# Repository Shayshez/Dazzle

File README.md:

# Dazzle
## CC-BY-SA 4.0
Rotatable Dual VC-Polarizer and VCA, Based on MI "Blinds".

## ROTATABLE = Modules for 3u / 1u
Dazzle comes with 2 panels: 1u/20hp and 3u/6hp

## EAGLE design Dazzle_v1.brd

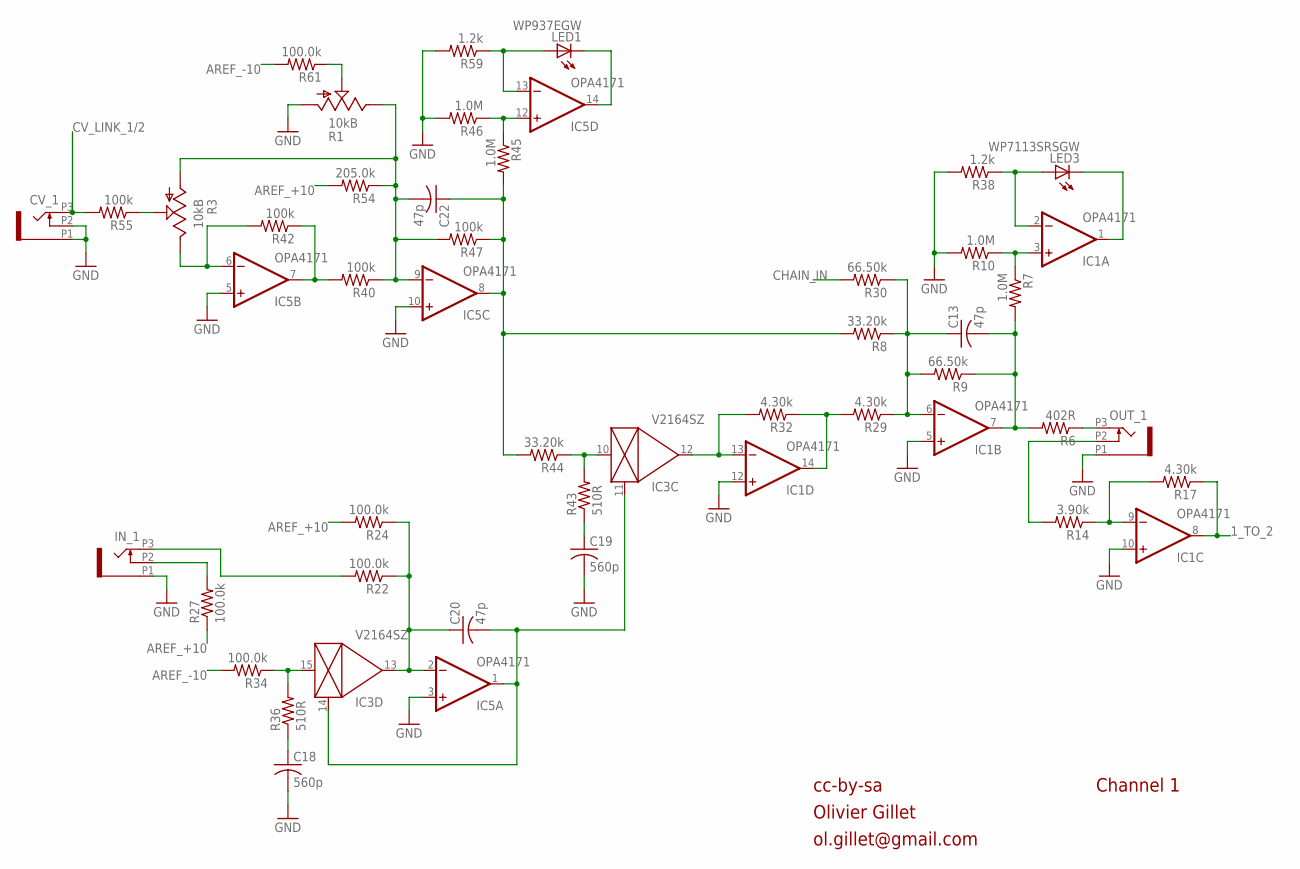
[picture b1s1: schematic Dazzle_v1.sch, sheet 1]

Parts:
C13, C20, C22: 47p; C0603
C18, C19: 560p; C0603
CV_1: OG-PJ301_PJ301_THONKICONN; OG-PJ301_WQP_PJ_301M6_NO_HOLE
IC1, IC5: OPA4171; TSSOP14
IC3: V2164SZ; SOIC16N
IN_1: OG-PJ301_PJ301_THONKICONN; OG-PJ301_WQP_PJ_301M6_NO_HOLE
LED1: WP937EGW; LED3MM
LED3: WP7113SRSGW; LED5MM
OUT_1: OG-PJ301_PJ301_THONKICONN; OG-PJ301_WQP_PJ_301M6_NO_HOLE
R1: 10kB; ALPS_POT_VERTICAL_PS
R3: 10kB; POT-ALPS_ALPS_POT_VERTICAL_PS
R6: 402R; R0603
R7, R10, R45, R46: 1.0M; R0603
R8, R44: 33.20k; R0603
R9, R30: 66.50k; R0603
R14: 3.90k; R0603
R17, R29, R32: 4.30k; R0603
R22, R24, R27, R34, R61: 100.0k; R0603
R36, R43: 510R; R0603
R38, R59: 1.2k; R0603
R40, R42, R47, R55: 100k; R0603
R54: 205.0k; R0603

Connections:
1_TO_2: IC1.8 (OUT), R17.1; also elsewhere on the board
AREF_+10: R24.2, R27.1, R54.2; also elsewhere on the board
AREF_-10: R34.2, R61.2; also elsewhere on the board
CHAIN_IN: R30.2; also elsewhere on the board
CV_LINK_1/2: CV_1.P3 (3), R55.2; also elsewhere on the board
FOO: IC3.15 (IN), R34.1, R36.2
GAIN_1: C22.1, IC5.8 (OUT), R8.2, R44.2, R45.2, R47.1
GND: C18.2, C19.2, CV_1.P1 (1), CV_1.P2 (2), IC1.5 (+IN), IC1.10 (+IN), IC1.12 (+IN), IC5.3 (+IN), IC5.5 (+IN), IC5.10 (+IN), IN_1.P1 (1), OUT_1.P1 (1), R1.P$3 (A), R10.2, R38.2, R46.2, R59.2; also elsewhere on the board
unnamed: R1.P$2 (S), R61.1
unnamed: IC1.13 (-IN), IC3.12 (OUT), R32.2
unnamed: IC5.14 (OUT), LED1.K (C)
unnamed: IC5.6 (-IN), R3.P$1 (E), R42.2
unnamed: OUT_1.P3 (3), R6.1
unnamed: IC5.7 (OUT), R40.2, R42.1
unnamed: C22.2, IC5.9 (-IN), R1.P$1 (E), R3.P$3 (A), R40.1, R47.2, R54.1
unnamed: C13.1, IC1.6 (-IN), R8.1, R9.2, R29.1, R30.1
unnamed: R3.P$2 (S), R55.1
unnamed: IC5.13 (-IN), LED1.A, R59.1
unnamed: IC1.1 (OUT), LED3.K (C)
unnamed: IC1.2 (-IN), LED3.A, R38.1
unnamed: C18.1, R36.1
unnamed: IN_1.P3 (3), R22.2
unnamed: IC1.9 (-IN), R14.1, R17.2
unnamed: OUT_1.P2 (2), R14.2
unnamed: C19.1, R43.1
unnamed: IN_1.P2 (2), R27.2
unnamed: IC1.14 (OUT), R29.2, R32.1
unnamed: C20.1, IC3.13 (OUT), IC5.2 (-IN), R22.1, R24.1
unnamed: C20.2, IC3.11 (CTRL), IC3.14 (CTRL), IC5.1 (OUT)
unnamed: IC3.10 (IN), R43.2, R44.1
unnamed: IC1.3 (+IN), R7.1, R10.1
unnamed: IC5.12 (+IN), R45.1, R46.1
OUT1: C13.2, IC1.7 (OUT), R6.2, R7.2, R9.1

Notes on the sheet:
cc-by-sa
Olivier Gillet
ol.gillet@gmail.com
Channel 1

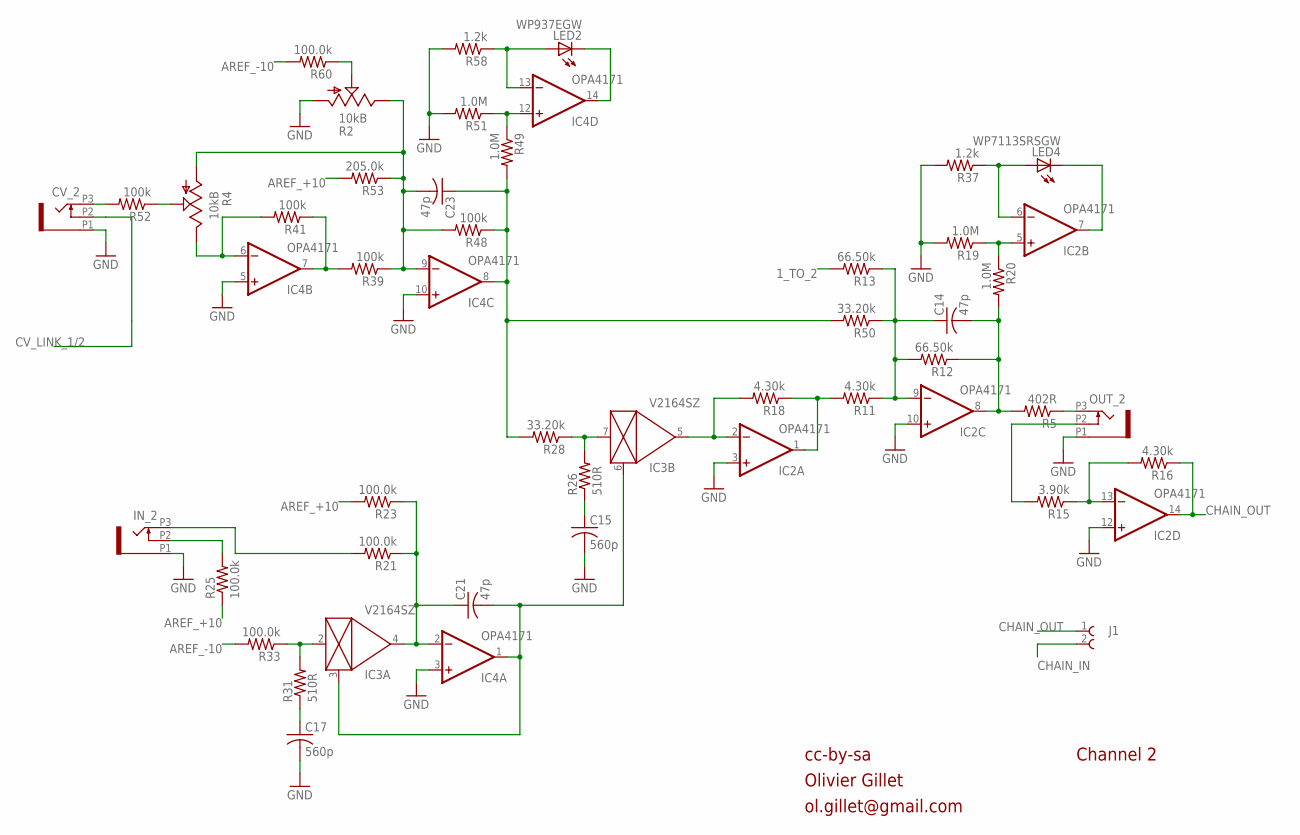
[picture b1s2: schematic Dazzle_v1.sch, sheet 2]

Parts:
C14, C21, C23: 47p; C0603
C15, C17: 560p; C0603
CV_2: OG-PJ301_PJ301_THONKICONN; OG-PJ301_WQP_PJ_301M6_NO_HOLE
IC2, IC4: OPA4171; TSSOP14
IC3: V2164SZ; SOIC16N
IN_2: OG-PJ301_PJ301_THONKICONN; OG-PJ301_WQP_PJ_301M6_NO_HOLE
J1: 61300211121
LED2: WP937EGW; LED3MM
LED4: WP7113SRSGW; LED5MM
OUT_2: OG-PJ301_PJ301_THONKICONN; OG-PJ301_WQP_PJ_301M6_NO_HOLE
R2: 10kB; ALPS_POT_VERTICAL_PS
R4: 10kB; POT-ALPS_ALPS_POT_VERTICAL_PS
R5: 402R; R0603
R11, R16, R18: 4.30k; R0603
R12, R13: 66.50k; R0603
R15: 3.90k; R0603
R19, R20, R49, R51: 1.0M; R0603
R21, R23, R25, R33, R60: 100.0k; R0603
R26, R31: 510R; R0603
R28, R50: 33.20k; R0603
R37, R58: 1.2k; R0603
R39, R41, R48, R52: 100k; R0603
R53: 205.0k; R0603

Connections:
1_TO_2: R13.2; also elsewhere on the board
AREF_+10: R23.2, R25.1, R53.2; also elsewhere on the board
AREF_-10: R33.2, R60.2; also elsewhere on the board
CHAIN_IN: J1.2; also elsewhere on the board
CHAIN_OUT: IC2.14 (OUT), J1.1, R16.1
CV_LINK_1/2: CV_2.P2 (2); also elsewhere on the board
FOO1: IC3.2 (IN), R31.2, R33.1
GAIN_2: C23.1, IC4.8 (OUT), R28.2, R48.1, R49.2, R50.2
GND: C15.2, C17.2, CV_2.P1 (1), IC2.3 (+IN), IC2.10 (+IN), IC2.12 (+IN), IC4.3 (+IN), IC4.5 (+IN), IC4.10 (+IN), IN_2.P1 (1), OUT_2.P1 (1), R2.P$3 (A), R19.2, R37.2, R51.2, R58.2; also elsewhere on the board
unnamed: OUT_2.P3 (3), R5.1
unnamed: C15.1, R26.1
unnamed: IC3.7 (IN), R26.2, R28.1
unnamed: IC2.2 (-IN), IC3.5 (OUT), R18.2
unnamed: C14.1, IC2.9 (-IN), R11.1, R12.2, R13.1, R50.1
unnamed: CV_2.P3 (3), R52.2
unnamed: IC4.6 (-IN), R4.P$1 (E), R41.2
unnamed: IC4.7 (OUT), R39.2, R41.1
unnamed: C23.2, IC4.9 (-IN), R2.P$1 (E), R4.P$3 (A), R39.1, R48.2, R53.1
unnamed: R2.P$2 (S), R60.1
unnamed: IC4.14 (OUT), LED2.K (C)
unnamed: IC4.13 (-IN), LED2.A, R58.1
unnamed: IC2.7 (OUT), LED4.K (C)
unnamed: IC2.6 (-IN), LED4.A, R37.1
unnamed: IC2.13 (-IN), R15.1, R16.2
unnamed: OUT_2.P2 (2), R15.2
unnamed: IC2.1 (OUT), R11.2, R18.1
unnamed: R4.P$2 (S), R52.1
unnamed: C17.1, R31.1
unnamed: C21.1, IC3.4 (OUT), IC4.2 (-IN), R21.1, R23.1
unnamed: C21.2, IC3.3 (CTRL), IC3.6 (CTRL), IC4.1 (OUT)
unnamed: IN_2.P3 (3), R21.2
unnamed: IN_2.P2 (2), R25.2
unnamed: IC2.5 (+IN), R19.1, R20.1
unnamed: IC4.12 (+IN), R49.1, R51.1
OUT2: C14.2, IC2.8 (OUT), R5.2, R12.1, R20.2

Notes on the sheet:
cc-by-sa
Olivier Gillet
ol.gillet@gmail.com
Channel 2

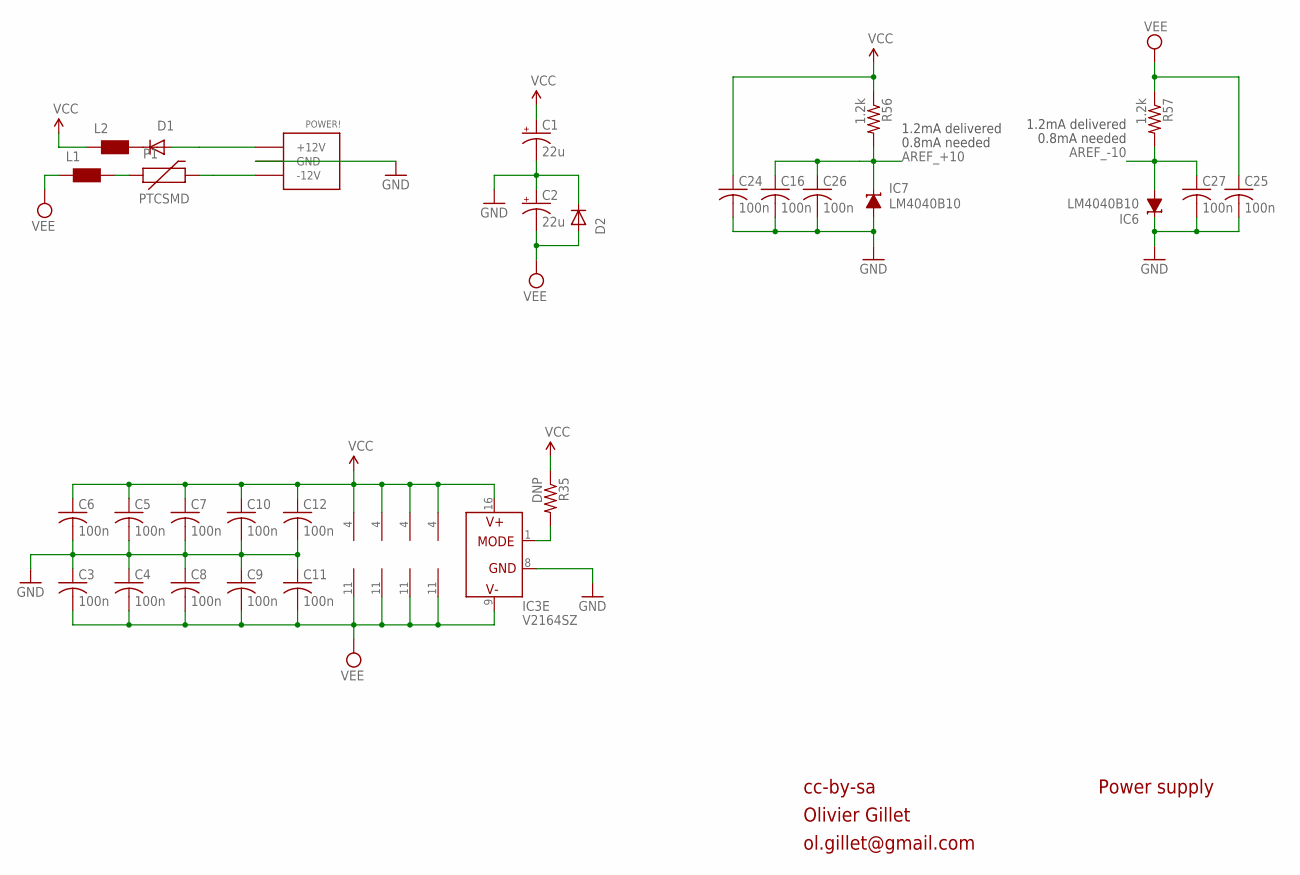
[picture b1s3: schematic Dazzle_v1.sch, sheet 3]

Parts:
C1, C2: 22u; PANASONIC_C
C3, C4, C5, C6, C7, C8, C9, C10, C11, C12, C16, C24, C25, C26, C27: 100n; C0603
D1, D2: 1N5819HW; SOD123
IC1, IC2, IC4, IC5: OPA4171; TSSOP14
IC3: V2164SZ; SOIC16N
IC6, IC7: LM4040B10; DBZ_R-PDSO-G3
L1, L2: WE-CBF_0603; 0603
P1: PTCSMD; PTC-1206
POWER!: POWER_SIMPLE; 2X05_SMT_HEADER
R35: DNP; R0603
R56, R57: 1.2k; R0603

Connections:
AREF_+10: C16.1, C26.1, IC7.1 (C), R56.2; also elsewhere on the board
AREF_-10: C27.1, IC6.2 (A), R57.2; also elsewhere on the board
GND: C1.-, C2.+, C3.1, C4.1, C5.2, C6.2, C7.2, C8.1, C9.1, C10.2, C11.1, C12.2, C16.2, C24.2, C25.2, C26.2, C27.2, D2.C, IC3.8 (GND), IC6.1 (C), IC7.2 (A), POWER!.3 (GND), POWER!.4 (GND), POWER!.5 (GND), POWER!.6 (GND), POWER!.7 (GND), POWER!.8 (GND); also elsewhere on the board
unnamed: IC3.1 (MODE), R35.2
unnamed: D1.A, POWER!.9 (+12V), POWER!.10 (+12V)
unnamed: P1.2, POWER!.1 (-12V), POWER!.2 (-12V)
unnamed: L1.2, P1.1
unnamed: D1.C, L2.2
VCC: C1.+, C5.1, C6.1, C7.1, C10.1, C12.1, C24.1, IC1.4 (V+), IC2.4 (V+), IC3.16 (V+), IC4.4 (V+), IC5.4 (V+), L2.1, R35.1, R56.1
VEE: C2.-, C3.2, C4.2, C8.2, C9.2, C11.2, C25.1, D2.A, IC1.11 (V-), IC2.11 (V-), IC3.9 (V-), IC4.11 (V-), IC5.11 (V-), L1.1, R57.1

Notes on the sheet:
cc-by-sa
Olivier Gillet
ol.gillet@gmail.com
Power supply
1.2mA delivered
0.8mA needed

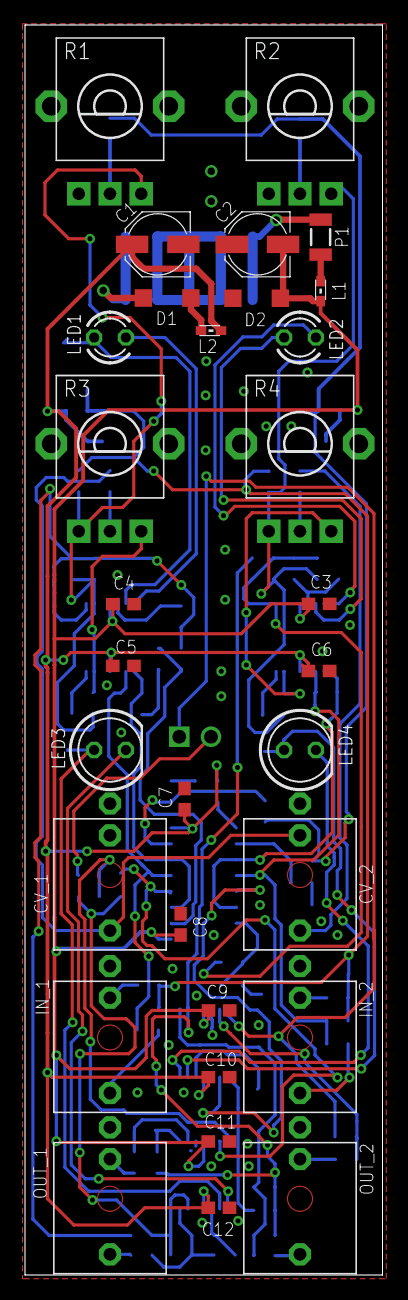
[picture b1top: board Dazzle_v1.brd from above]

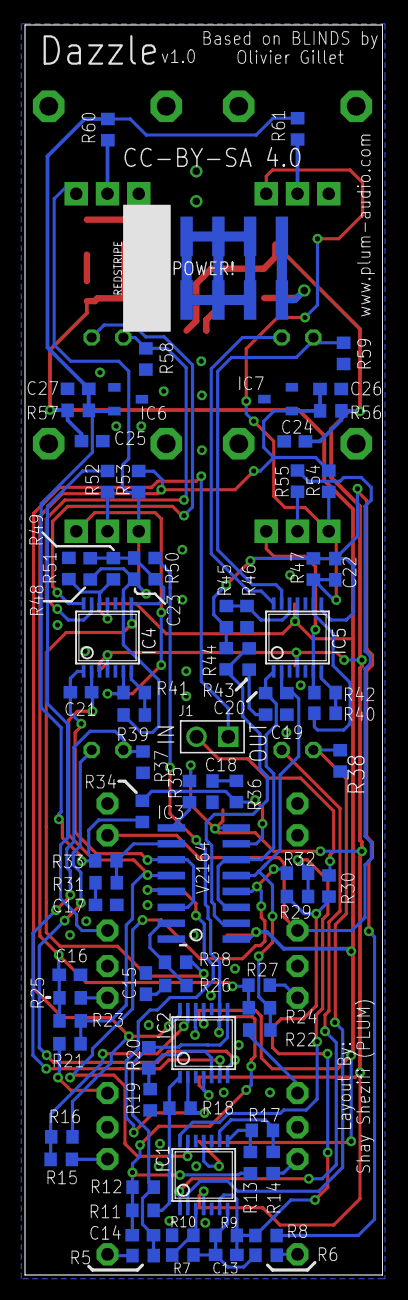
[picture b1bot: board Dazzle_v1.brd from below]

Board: 2 copper layers, 28.6 x 100.0 mm, 112 parts (81 on the bottom side), 69 nets.

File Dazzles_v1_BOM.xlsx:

Qty | Value | Device | Package | Parts | Description
1 | DNP | Resistor, 1% | R0603 | R35 | RESISTOR, American symbol
2 | 402R | Resistor, 1% | R0603 | R5, R6 | RESISTOR, American symbol
4 | 510R | Resistor, 1% | R0603 | R26, R31, R36, R43 | RESISTOR, American symbol
6 | 1.2k | Resistor, 1% | R0603 | R37, R38, R56, R57, R58, R59 | RESISTOR, American symbol
2 | 3.90k | Resistor, 0.1%, thin film | R0603 | R14, R15 | RESISTOR, American symbol
6 | 4.30k | Resistor, 0.1%, thin film | R0603 | R11, R16, R17, R18, R29, R32 | RESISTOR, American symbol
4 | 33.20k | Resistor, 0.1%, thin film | R0603 | R8, R28, R44, R50 | RESISTOR, American symbol
4 | 66.50k | Resistor, 0.1%, thin film | R0603 | R9, R12, R13, R30 | RESISTOR, American symbol
10 | 100.0k | Resistor, 0.1%, thin film | R0603 | R21, R22, R23, R24, R25, R27, R33, R34, R60, R61 | RESISTOR, American symbol
8 | 100k | Resistor, 1% | R0603 | R39, R40, R41, R42, R47, R48, R52, R55 | RESISTOR, American symbol
2 | 205.0k | Resistor, 0.1%, thin film | R0603 | R53, R54 | RESISTOR, American symbol
8 | 1.0M | Resistor, 1% | R0603 | R7, R10, R19, R20, R45, R46, R49, R51 | RESISTOR, American symbol
6 | 47p | Capacitor, ceramic, C0G >= 50V, 1% | C0603 | C13, C14, C20, C21, C22, C23 | CAPACITOR, American symbol
4 | 560p | Capacitor, ceramic, C0G | C0603 | C15, C17, C18, C19 | CAPACITOR, American symbol
15 | 100n | C-USC0603 | C0603 | C3, C4, C5, C6, C7, C8, C9, C10, C11, C12, C16, C24, C25, C26, C27 | CAPACITOR, American symbol
2 | 22u | CPOL-USC | PANASONIC_C | C1, C2 | POLARIZED CAPACITOR, American symbol
1 | PTCSMD | PTCSMD | PTC-1206 | P1 | Resettable Fuse PTC
2 | Ferrite Beads | WE-CBF_0603 | L0603 | L1, L2 | SMD EMI Suppression Ferrite Beads
2 | 1N5819HW | DIODE-SOD123 | SOD123 | D1, D2 | DIODE
2 | LM4040B10 | LM4041B12DBZ | DBZ_R-PDSO-G3 | IC6, IC7 | PRECISION MICROPOWER SHUNT VOLTAGE REFERENCE
4 | OPA4171 | TL074PW | TSSOP14 | IC1, IC2, IC4, IC5 | OP AMP
1 | V2164SZ | SSM2164S | SOIC16N | IC3
2 | WP7113SRSGW | LED5MM | LED5MM | LED3, LED4 | LED
2 | WP937EGW | LED3MM | LED3MM | LED1, LED2 | LED
1 | MIX IN/OUT | 2 * 1 2.54mm Pin Header | 2.54mm Pin Header | J1 | WR-PHD 2.54mm Pin Header, 2 Pin=>Code : Con_BTB_PHD_2.54_1_THT_61300211121
2 | 10kB | POT_USVERTICAL_PS | ALPS_POT_VERTICAL_PS | R1, R2
2 | 10kB | POT-ALPS_POT_USVERTICAL_PS | POT-ALPS_ALPS_POT_VERTICAL_PS | R3, R4
1 | POWER_SIMPLE | POWER_SIMPLE | 2X05_SMT_HEADER | POWER!
6 | OG-PJ301_PJ301_THONKICONN | OG-PJ301_PJ301_THONKICONN | OG-PJ301_WQP_PJ_301M6_NO_HOLE | CV_1, CV_2, IN_1, IN_2, OUT_1, OUT_2

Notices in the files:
parts and their libraries:
Wurth_Elektronik_Electromechanic_Board_t: Copyright: Würth Elektronik
